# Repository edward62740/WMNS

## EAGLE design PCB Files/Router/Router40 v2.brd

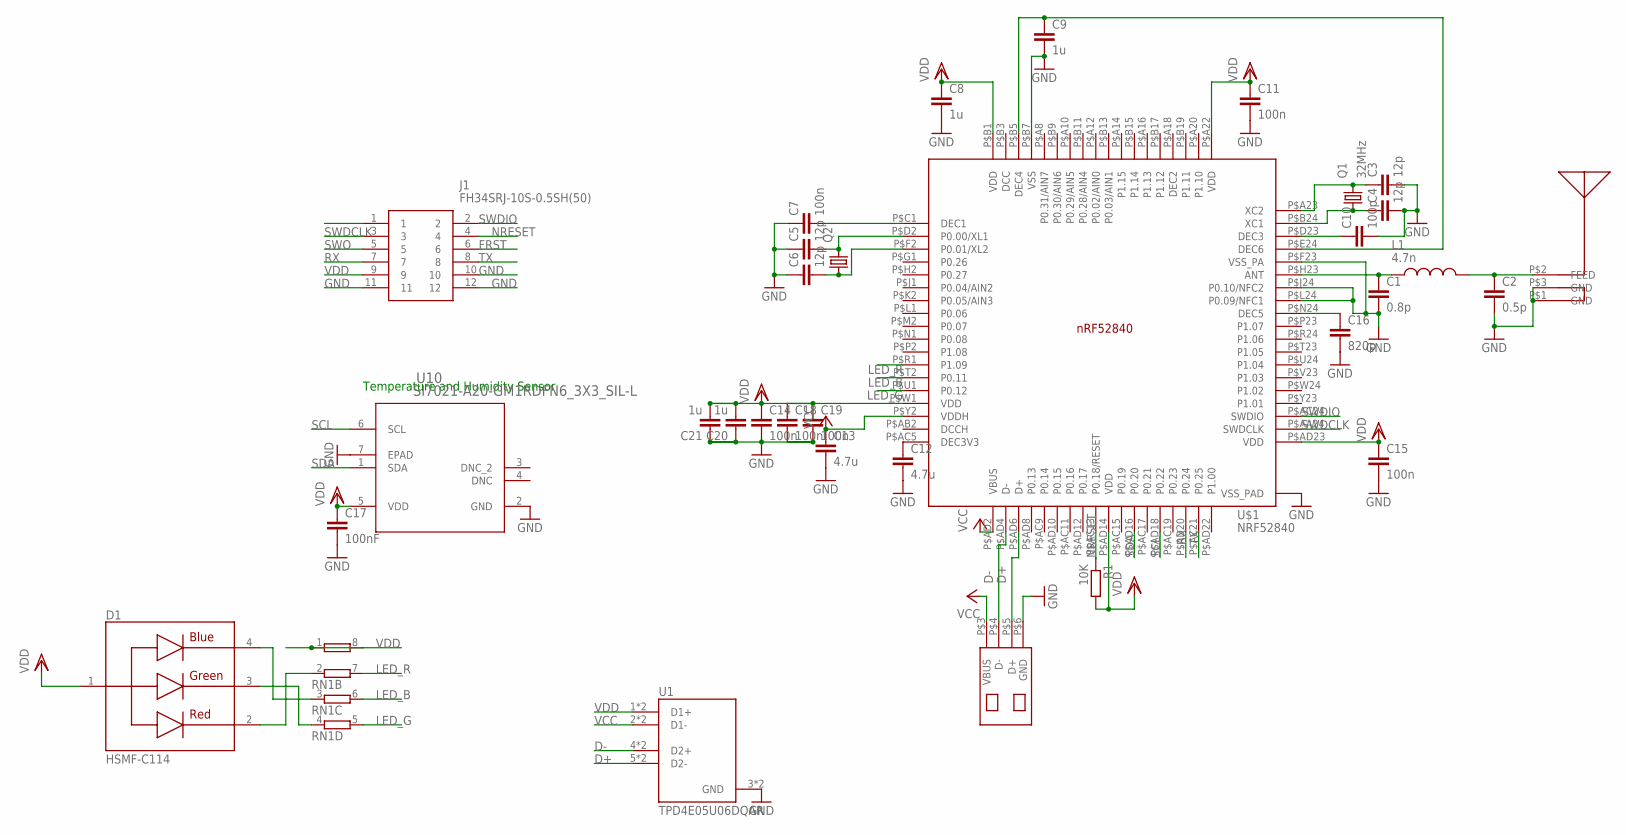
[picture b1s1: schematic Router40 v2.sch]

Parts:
C1: 0.8p; C0402
C2: 0.5p; C0402
C3, C4, C5, C6: 12p; C0402
C7, C11, C14, C15, C18, C19: 100n; C0402
C8, C9: 1u; C0402
C10: 100p; C0402
C12, C13: 4.7u; C0402
C16: 820p; C0402
C17: 100nF; C0402
C20, C21: 1u; C0603R
D1: HSMF-C114; DIOSC160X150X35-4N
J1: FH34SRJ-10S-0.5SH(50); FH34SRJ10S05SH50
L1: 4.7n; INDC0402X26N
Q1: 32MHz; 2.0X1.6_KX-5
Q2: KX-327-RT; 2.0X1.2
R1: 10K; R0402
RN1: 4R-N0402ARV341; 4X0402ARV341
U1: TPD4E05U06DQAR; TI_TPD4E05U06DQAR
U10: SI7021-A20-GM1RDFN6_3X3_SIL-L; DFN6_3X3_SIL-L
U$1: NRF52840; AQFN50P700X700X85_HS-74N
U$2: USBA_MALE
U$4: CHIPANTENNAL2

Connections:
D+: U1.5 (D2-), U1.6 (D2-), U$1.P$AD6 (D+), U$2.P$5 (D+)
D-: U1.4 (D2+), U1.7 (D2+), U$1.P$AD4 (D-), U$2.P$4 (D-)
FRST: J1.6
GND: C1.2, C2.2, C3.2, C4.2, C5.1, C6.1, C7.1, C8.2, C9.2, C10.2, C11.2, C12.2, C13.2, C14.2, C15.2, C16.2, C17.2, C18.2, C19.2, C20.1, C21.1, J1.10, J1.11, J1.12, U1.3 (GND), U1.8 (GND), U10.2 (GND), U10.7 (EPAD), U$1.P$74 (VSS_PAD), U$1.P$75 (VSS_PAD), U$1.P$76 (VSS_PAD), U$1.P$77 (VSS_PAD), U$1.P$78 (VSS_PAD), U$1.P$79 (VSS_PAD), U$1.P$80 (VSS_PAD), U$1.P$81 (VSS_PAD), U$1.P$82 (VSS_PAD), U$1.P$83 (VSS_PAD), U$1.P$84 (VSS_PAD), U$1.P$85 (VSS_PAD), U$1.P$86 (VSS_PAD), U$1.P$87 (VSS_PAD), U$1.P$88 (VSS_PAD), U$1.P$89 (VSS_PAD), U$1.P$90 (VSS_PAD), U$1.P$B7 (VSS), U$1.P$F23 (VSS_PA), U$1.P$J24 (P0.10/NFC2), U$1.P$L24 (P0.09/NFC1), U$2.P$6 (GND), U$4.P$1 (GND), U$4.P$3 (GND)
LED_B: RN1.6 (2), U$1.P$T2 (P0.11)
LED_G: RN1.5 (2), U$1.P$U1 (P0.12)
LED_R: RN1.7 (2), U$1.P$R1 (P1.09)
unnamed: C1.1, L1.1, U$1.P$H23 (ANT)
unnamed: C2.1, L1.2, U$4.P$2 (FEED)
unnamed: C3.1, Q1.3 (2), U$1.P$A23 (XC2)
unnamed: C4.1, Q1.1, U$1.P$B24 (XC1)
unnamed: C5.2, Q2.2, U$1.P$D2 (P0.00/XL1)
unnamed: C6.2, Q2.1, U$1.P$F2 (P0.01/XL2)
unnamed: C7.2, U$1.P$C1 (DEC1)
unnamed: C9.1, U$1.P$B5 (DEC4), U$1.P$E24 (DEC6)
unnamed: C10.1, U$1.P$D23 (DEC3)
unnamed: C12.1, U$1.P$AC5 (DEC3V3)
unnamed: C16.1, U$1.P$N24 (DEC5)
unnamed: D1.2, RN1.2 (1)
unnamed: D1.3, RN1.4 (1)
unnamed: D1.4, RN1.3 (1)
NRESET: J1.4, R1.1, U$1.P$AC13 (P0.18/RESET)
RX: J1.7, U$1.P$AD20 (P0.24)
SCL: U10.6 (SCL), U$1.P$AD18 (P0.22)
SDA: U10.1 (SDA), U$1.P$AD16 (P0.20)
SWDCLK: J1.3, U$1.P$AA24 (SWDCLK)
SWDIO: J1.2, U$1.P$AC24 (SWDIO)
SWO: J1.5
TX: J1.8, U$1.P$AC21 (P0.25)
VCC: C13.1, U1.2 (D1-), U1.9 (D1-), U$1.P$AD2 (VBUS), U$1.P$Y2 (VDDH), U$2.P$3 (VBUS)
VDD: C8.1, C11.1, C14.1, C15.1, C17.1, C18.1, C19.1, C20.2, C21.2, D1.1, J1.9, R1.2, RN1.1, RN1.8 (2), U1.1 (D1+), U1.10 (D1+), U10.5 (VDD), U$1.P$A22 (VDD), U$1.P$AD14 (VDD), U$1.P$AD23 (VDD), U$1.P$B1 (VDD), U$1.P$W1 (VDD)

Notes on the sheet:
Temperature and Humidity Sensor

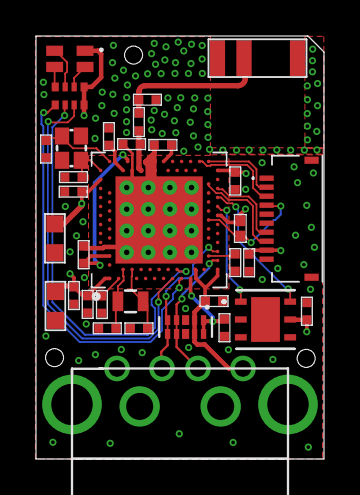
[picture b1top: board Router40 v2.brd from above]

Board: 4 copper layers, 16.0 x 23.5 mm, 33 parts (0 on the bottom side), 29 nets.

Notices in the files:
parts and their libraries:
crystal-geyer_V1_0: Copyright: Geyer-Electronic
COPYRIGHT: Copyright (C) 2018 Accelerated Designs. All rights reserved
